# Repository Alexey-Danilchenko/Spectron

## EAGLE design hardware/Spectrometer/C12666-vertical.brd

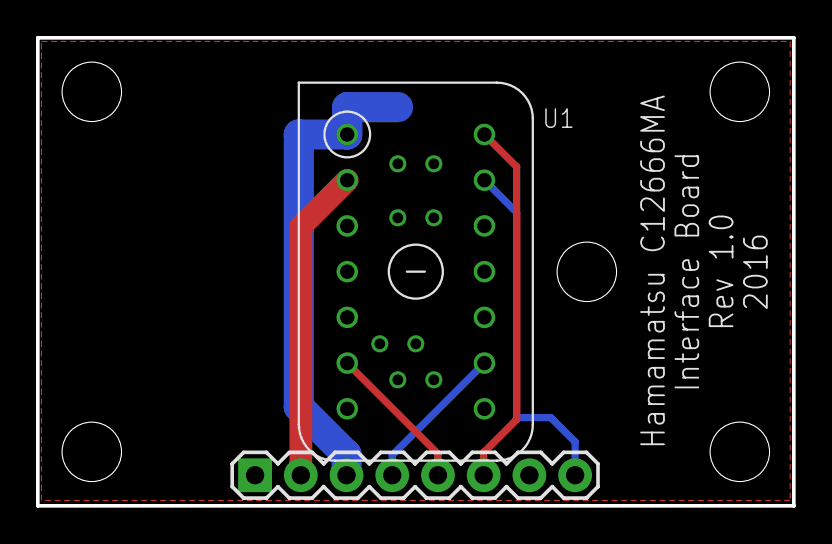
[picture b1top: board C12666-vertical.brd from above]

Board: 2 copper layers, 42.0 x 26.0 mm, 8 parts (1 on the bottom side), 7 nets.

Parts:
C1: 0.1 uF; C0805
JP1: 1X08
STANDOFF1, STANDOFF2, STANDOFF3, STANDOFF4, STANDOFF5: STAND-OFF
U1: MICROSPEC-C12666MA; C12666MA

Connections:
CLK: JP1.5, U1.4
EOS: JP1.6, U1.10
GAIN: JP1.8, U1.9
GND: C1.2, JP1.1, U1.3, U1.5
ST: JP1.4, U1.7
VDD: C1.1, JP1.3, U1.1
VIDEO: JP1.2, U1.2

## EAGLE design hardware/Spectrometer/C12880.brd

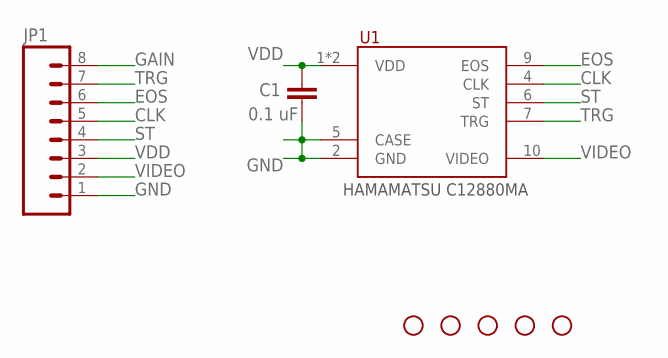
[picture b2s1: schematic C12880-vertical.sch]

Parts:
C1: 0.1 uF; C0805
JP1: M08SILK_FEMALE_PTH; 1X08
STANDOFF1, STANDOFF2, STANDOFF3, STANDOFF4, STANDOFF5: STAND-OFF
U1: MICROSPEC-C12880MA; C12880MA

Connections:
CLK: JP1.5, U1.4 (CLK)
EOS: JP1.6, U1.9 (EOS)
GAIN: JP1.8
GND: C1.2, JP1.1, U1.2 (GND), U1.5 (CASE)
ST: JP1.4, U1.6 (ST)
TRG: JP1.7, U1.7 (TRG)
VDD: C1.1, JP1.3, U1.1 (VDD), U1.3 (VDD)
VIDEO: JP1.2, U1.10 (VIDEO)

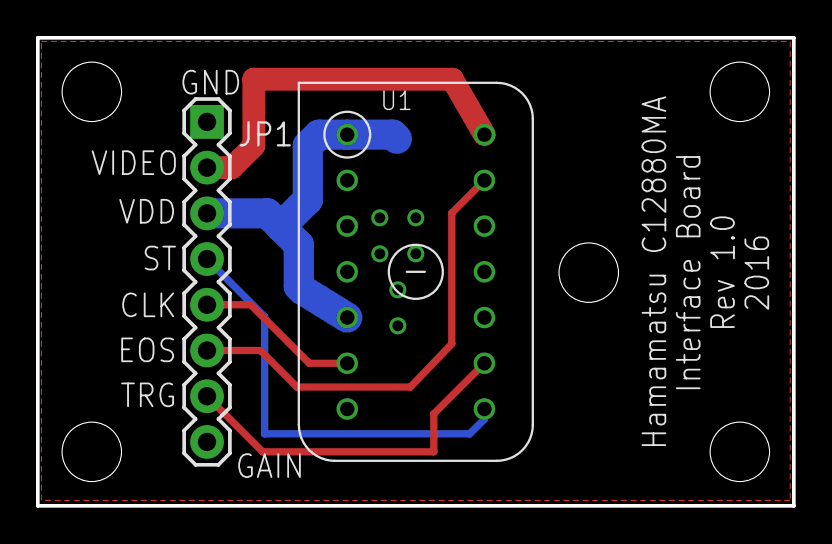
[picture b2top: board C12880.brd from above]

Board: 2 copper layers, 42.0 x 26.0 mm, 8 parts (1 on the bottom side), 7 nets.

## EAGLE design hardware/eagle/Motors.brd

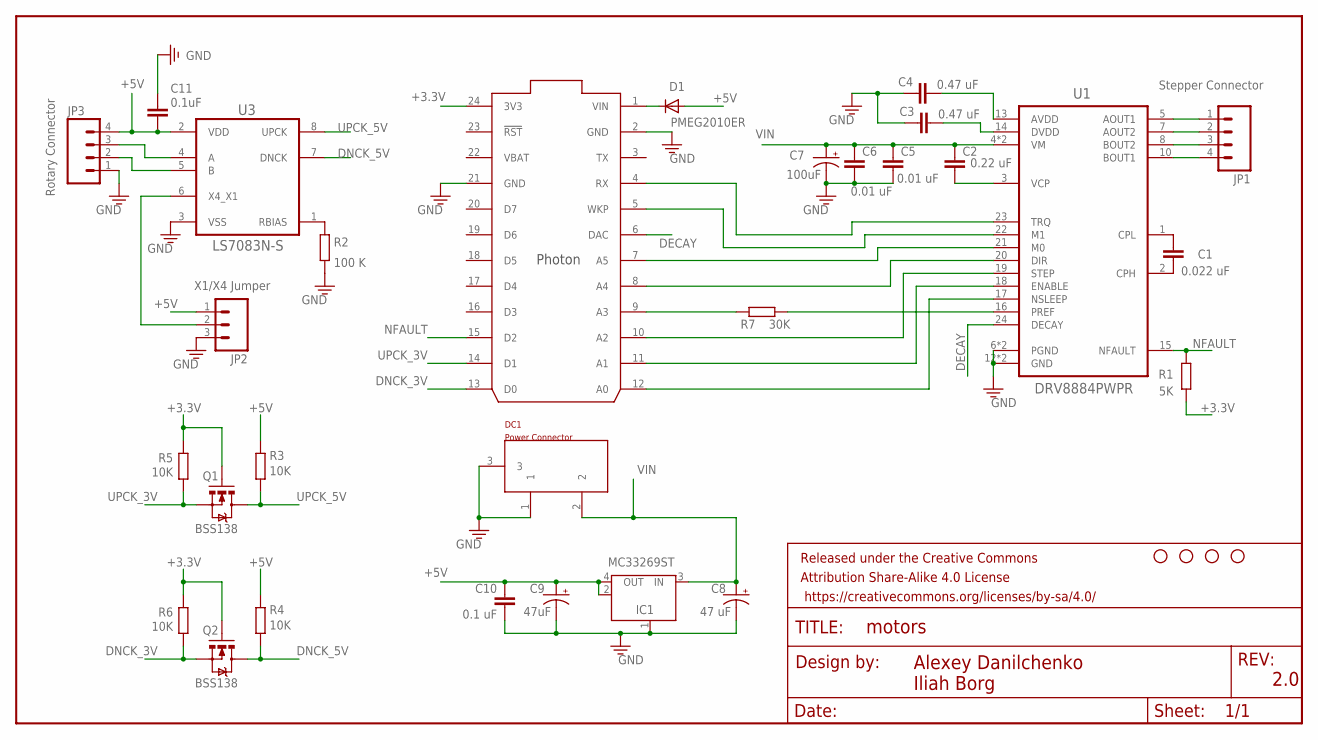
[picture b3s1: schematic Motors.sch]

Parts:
C1: 0.022 uF; C0805
C2: 0.22 uF; C0805
C3, C4: 0.47 uF; C0805
C5, C6: 0.01 uF; C0805
C7: 100uF; CT7343
C8: 47 uF; CT7343
C9: 47uF; CT7343
C10: 0.1 uF; C0805
C11: 0.1uF; C0805
D1: PMEG2010ER; SOD123
DC1: Power Connector; POWERSUPPLY_DC-21MM
FRAME1: FRAME-LETTER; CREATIVE_COMMONS
IC1: MC33269ST; SOT223
JP1: Stepper Connector; 1X04
JP2: X1/X4 Jumper; 1X03
JP3: Rotary Connector; 1X04
Q1, Q2: BSS138; SOT23-3
R1: 5K; R0805
R2: 100 K; R0805
R3, R4, R5, R6: 10K; R0805
R7: 30K; R0805
STANDOFF1, STANDOFF2, STANDOFF3, STANDOFF4: STAND-OFF
U1: DRV8884PWPR; SOP65P640X120-29N
U2: PHOTON_WITH_HEADERS; PHOTON
U3: LS7083N-S; SOIC127P600X175-8N

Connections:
+3.3V: Q1.1 (G), Q2.1 (G), R1.1, R5.1, R6.1, U2.24 (3V3)
+5V: C9.+, C10.1, C11.2, D1.A, IC1.2 (OUT), IC1.4 (OUT), JP2.1, JP3.4, R3.1, R4.1, U3.2 (VDD)
DECAY: U1.24 (DECAY), U2.6 (DAC)
DNCK_3V: Q2.2 (S), R6.2, U2.13 (D0)
DNCK_5V: Q2.3 (D), R4.2, U3.7 (DNCK)
GND: C3.2, C4.2, C5.2, C6.2, C7.-, C8.-, C9.-, C10.2, C11.1, DC1.1, DC1.3, IC1.1 (GND/ADJ), JP2.3, JP3.1, R2.2, U1.6 (PGND), U1.9 (PGND), U1.12 (GND), U1.25 (GND), U2.2 (GND), U2.21 (GND), U3.3 (VSS)
unnamed: U1.18 (ENABLE), U2.11 (A1)
unnamed: C2.2, U1.3 (VCP)
unnamed: C1.1, U1.2 (CPH)
unnamed: C1.2, U1.1 (CPL)
unnamed: U1.22 (M1), U2.5 (WKP)
unnamed: U1.17 (NSLEEP), U2.12 (A0)
unnamed: R7.1, U1.16 (PREF)
unnamed: C4.1, U1.13 (AVDD)
unnamed: C3.1, U1.14 (DVDD)
unnamed: D1.C, U2.1 (VIN)
unnamed: U1.19 (STEP), U2.10 (A2)
unnamed: U1.20 (DIR), U2.8 (A4)
unnamed: U1.21 (M0), U2.7 (A5)
unnamed: U1.23 (TRQ), U2.4 (RX)
unnamed: R7.2, U2.9 (A3)
unnamed: R2.1, U3.1 (RBIAS)
unnamed: JP1.1, U1.5 (AOUT1)
unnamed: JP1.2, U1.7 (AOUT2)
unnamed: JP2.2, U3.6 (X4_X1)
unnamed: JP1.3, U1.8 (BOUT2)
unnamed: JP1.4, U1.10 (BOUT1)
NFAULT: R1.2, U1.15 (NFAULT), U2.15 (D2)
ROTARY_A: JP3.3, U3.4 (A)
ROTARY_B: JP3.2, U3.5 (B)
UPCK_3V: Q1.2 (S), R5.2, U2.14 (D1)
UPCK_5V: Q1.3 (D), R3.2, U3.8 (UPCK)
VBAT: U2.22 (VBAT)
VIN: C2.1, C5.1, C6.1, C7.+, C8.+, DC1.2, IC1.3 (IN), U1.4 (VM), U1.11 (VM)

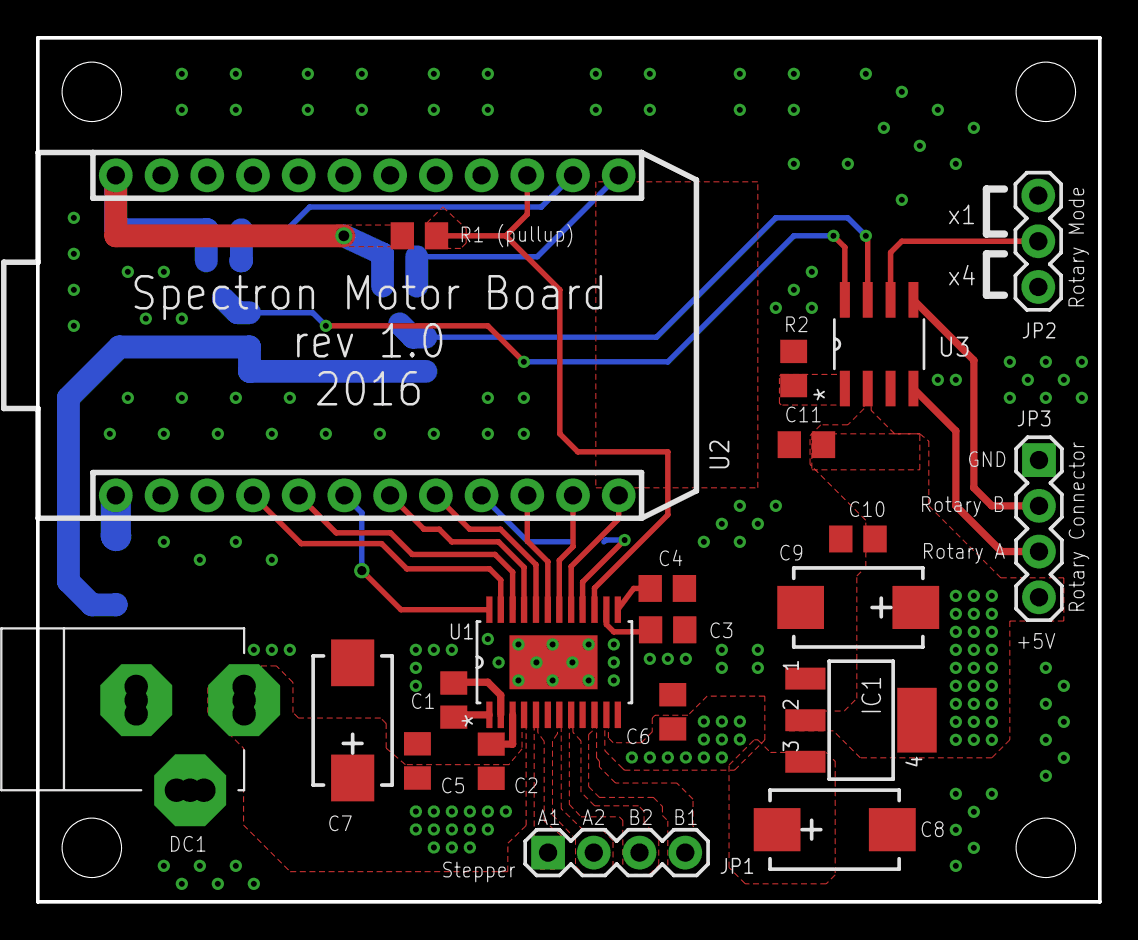
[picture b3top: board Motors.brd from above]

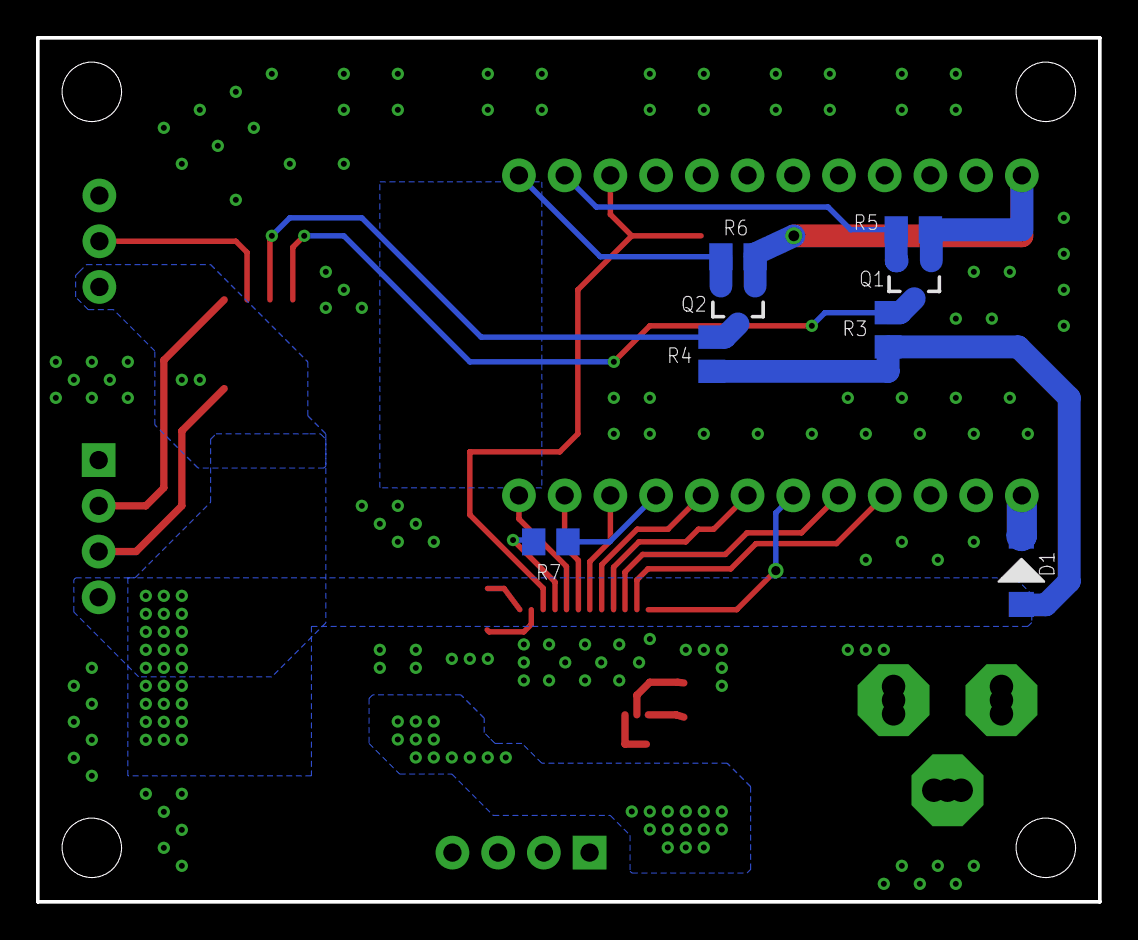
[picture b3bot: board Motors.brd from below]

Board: 2 copper layers, 59.0 x 48.0 mm, 34 parts (8 on the bottom side), 33 nets.

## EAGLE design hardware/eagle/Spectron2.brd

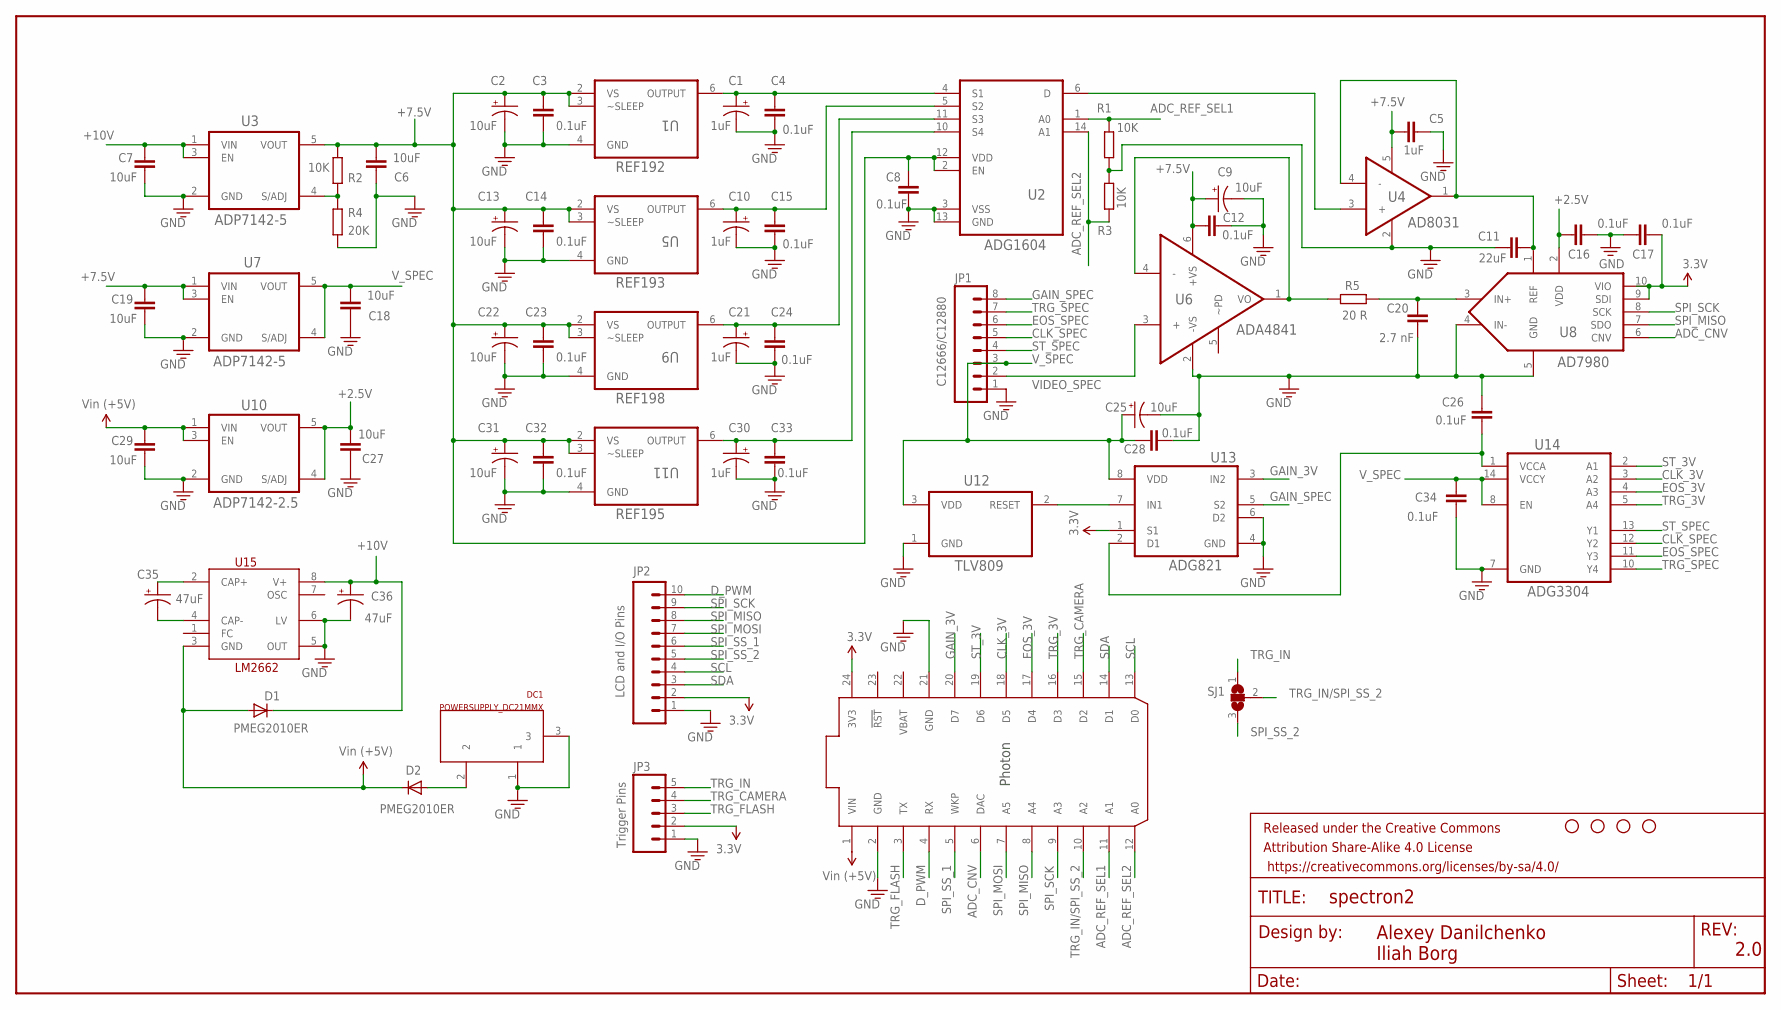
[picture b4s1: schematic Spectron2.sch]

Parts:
C1, C10, C21, C30: 1uF; EIA3216
C2, C9, C13, C22, C25, C31: 10uF; EIA3216
C3, C4, C8, C12, C14, C15, C16, C17, C23, C24, C26, C28, C32, C33, C34: 0.1uF; C0805
C5: 1uF; C0805
C6, C7, C18, C19, C27, C29: 10uF; C0805
C11: 22uF; 1206
C20: 2.7 nF; C0805
C35, C36: 47uF; CT7343
D1, D2: PMEG2010ER; SOD123
DC1: POWERSUPPLY_DC21MMX; POWERSUPPLY_DC-21MM
FRAME1: FRAME-LEDGER; CREATIVE_COMMONS
JP1: C12666/C12880; 1X08
JP2: LCD and I/O Pins; 1X10
JP3: Trigger Pins; 1X05
R1, R2, R3: 10K; R0805
R4: 20K; R0805
R5: 20 R; R0805
SJ1: SJ2W; SJ_2
STANDOFF1, STANDOFF2, STANDOFF3, STANDOFF4: STAND-OFF
U1: REF192; SOIC127P600X175-8N
U2: ADG1604; SOP65P640X120-14N
U3, U7: ADP7142-5; SOT95P280X145-5N
U4: AD8031; SOT95P280X145-5N
U5: REF193; SOIC127P600X175-8N
U6: ADA4841; SOT95P280X145-6N
U8: AD7980; SOP50P490X110-10N
U9: REF198; SOIC127P600X175-8N
U10: ADP7142-2.5; SOT95P280X145-5N
U11: REF195; SOIC127P600X175-8N
U12: TLV809; SOT95P237X112-3N
U13: ADG821; SOP65P490X110-8N
U14: ADG3304; SOP65P640X120-14N
U15: LM2662; SOIC8
U16: PHOTON_WITH_HEADERS; PHOTON

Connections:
3.3V: C17.2, JP2.2, JP3.2, U8.9 (SDI), U8.10 (VIO), U13.1 (S1), U16.24 (3V3)
+2.5V: C16.1, C27.1, U8.2 (VDD), U10.4 (S/ADJ), U10.5 (VOUT)
+7.5V: C2.A (+), C3.2, C5.2, C6.1, C8.2, C9.A (+), C12.2, C13.A (+), C14.2, C19.2, C22.A (+), C23.2, C31.A (+), C32.2, R2.1, U1.2 (VS), U1.3 (~SLEEP), U2.2 (EN), U2.12 (VDD), U3.5 (VOUT), U4.5 (+VS), U5.2 (VS), U5.3 (~SLEEP), U6.6 (+VS), U7.1 (VIN), U7.3 (EN), U9.2 (VS), U9.3 (~SLEEP), U11.2 (VS), U11.3 (~SLEEP)
+10V: C7.2, C36.+, D1.C, U3.1 (VIN), U3.3 (EN), U15.8 (V+)
ADC_CNV: U8.6 (CNV), U16.6 (DAC)
ADC_REF_SEL1: R1.1, U2.1 (A0), U16.11 (A1)
ADC_REF_SEL2: R3.2, U2.14 (A1), U16.12 (A0)
CLK_3V: U14.3 (A2), U16.18 (D5)
CLK_SPEC: JP1.5, U14.12 (Y2)
D_PWM: JP2.10, U16.4 (RX)
EOS_3V: U14.4 (A3), U16.17 (D4)
EOS_SPEC: JP1.6, U14.11 (Y3)
GAIN_3V: U13.3 (IN2), U16.20 (D7)
GAIN_SPEC: JP1.8, U13.5 (S2)
GND: C1.C (-), C2.C (-), C3.1, C4.1, C5.1, C6.2, C7.1, C8.1, C9.C (-), C10.C (-), C11.1, C12.1, C13.C (-), C14.1, C15.1, C16.2, C17.1, C18.2, C19.1, C20.1, C21.C (-), C22.C (-), C23.1, C24.1, C25.C (-), C26.2, C27.2, C28.1, C29.1, C30.C (-), C31.C (-), C32.1, C33.1, C34.1, C36.-, DC1.1, DC1.3, JP1.1, JP2.1, JP3.1, R1.2, R3.1, R4.2, U1.4 (GND), U2.3 (VSS), U2.13 (GND), U3.2 (GND), U4.2 (-VS), U5.4 (GND), U6.2 (-VS), U7.2 (GND), U8.4 (IN-), U8.5 (GND), U9.4 (GND), U10.2 (GND), U11.4 (GND), U12.1 (GND), U13.4 (GND), U13.6 (D2), U14.7 (GND), U15.5 (OUT), U15.6 (LV), U16.2 (GND), U16.21 (GND)
unnamed: R2.2, R4.1, U3.4 (S/ADJ)
unnamed: C11.2, U4.1 (VOUT), U4.4 (-), U8.1 (REF)
unnamed: C21.A (+), C24.2, U2.11 (S3), U9.6 (OUTPUT)
unnamed: R5.2, U6.1 (VO), U6.4 (-)
unnamed: U12.2 (RESET), U13.7 (IN1)
unnamed: C1.A (+), C4.2, U1.6 (OUTPUT), U2.4 (S1)
unnamed: U2.6 (D), U4.3 (+)
unnamed: C10.A (+), C15.2, U2.5 (S2), U5.6 (OUTPUT)
unnamed: C30.A (+), C33.2, U2.10 (S4), U11.6 (OUTPUT)
unnamed: D2.A, DC1.2
unnamed: C20.2, R5.1, U8.3 (IN+)
unnamed: C35.-, U15.4 (CAP-)
unnamed: C35.+, U15.2 (CAP+)
unnamed: C26.1, U13.2 (D1), U14.1 (VCCA)
SCL: JP2.4, U16.13 (D0)
SDA: JP2.3, U16.14 (D1)
SPI_MISO: JP2.8, U8.7 (SDO), U16.8 (A4)
SPI_MOSI: JP2.7, U16.7 (A5)
SPI_SCK: JP2.9, U8.8 (SCK), U16.9 (A3)
SPI_SS_1: JP2.6, U16.5 (WKP)
SPI_SS_2: JP2.5, SJ1.3
ST_3V: U14.2 (A1), U16.19 (D6)
ST_SPEC: JP1.4, U14.13 (Y1)
TRG_3V: U14.5 (A4), U16.16 (D3)
TRG_CAMERA: JP3.4, U16.15 (D2)
TRG_FLASH: JP3.3, U16.3 (TX)
TRG_IN: JP3.5, SJ1.1
TRG_IN/SPI_SS_2: SJ1.2, U16.10 (A2)
TRG_SPEC: JP1.7, U14.10 (Y4)
VBAT: U16.22 (VBAT)
VIDEO_SPEC: JP1.2, U6.3 (+)
VIN: C29.2, D1.A, D2.C, U10.1 (VIN), U10.3 (EN), U15.3 (GND), U16.1 (VIN)
V_SPEC: C18.1, C25.A (+), C28.2, C34.2, JP1.3, U7.4 (S/ADJ), U7.5 (VOUT), U12.3 (VDD), U13.8 (VDD), U14.8 (EN), U14.14 (VCCY)

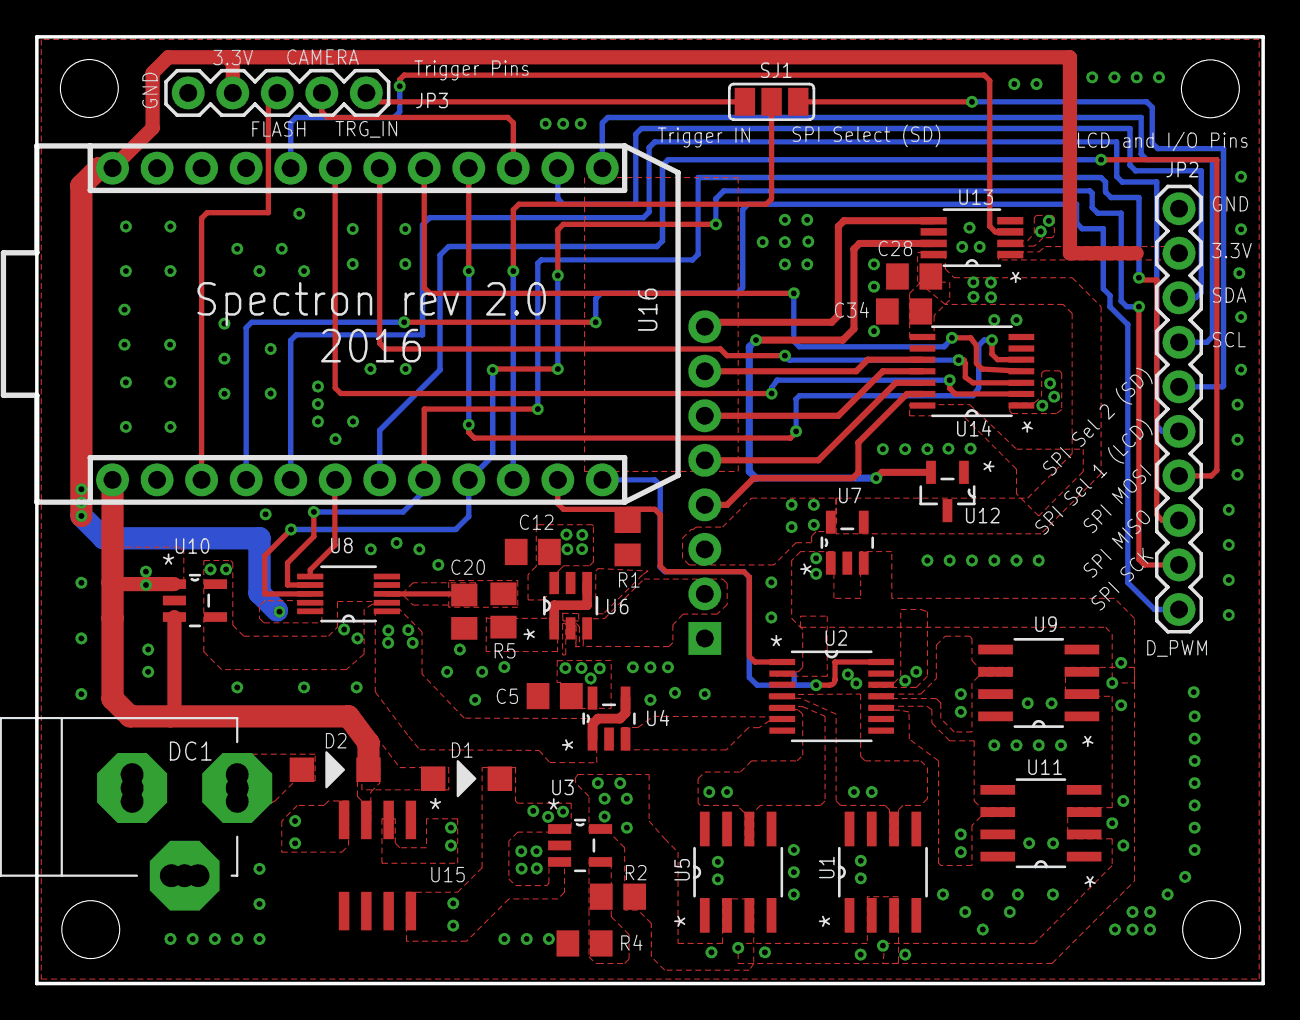
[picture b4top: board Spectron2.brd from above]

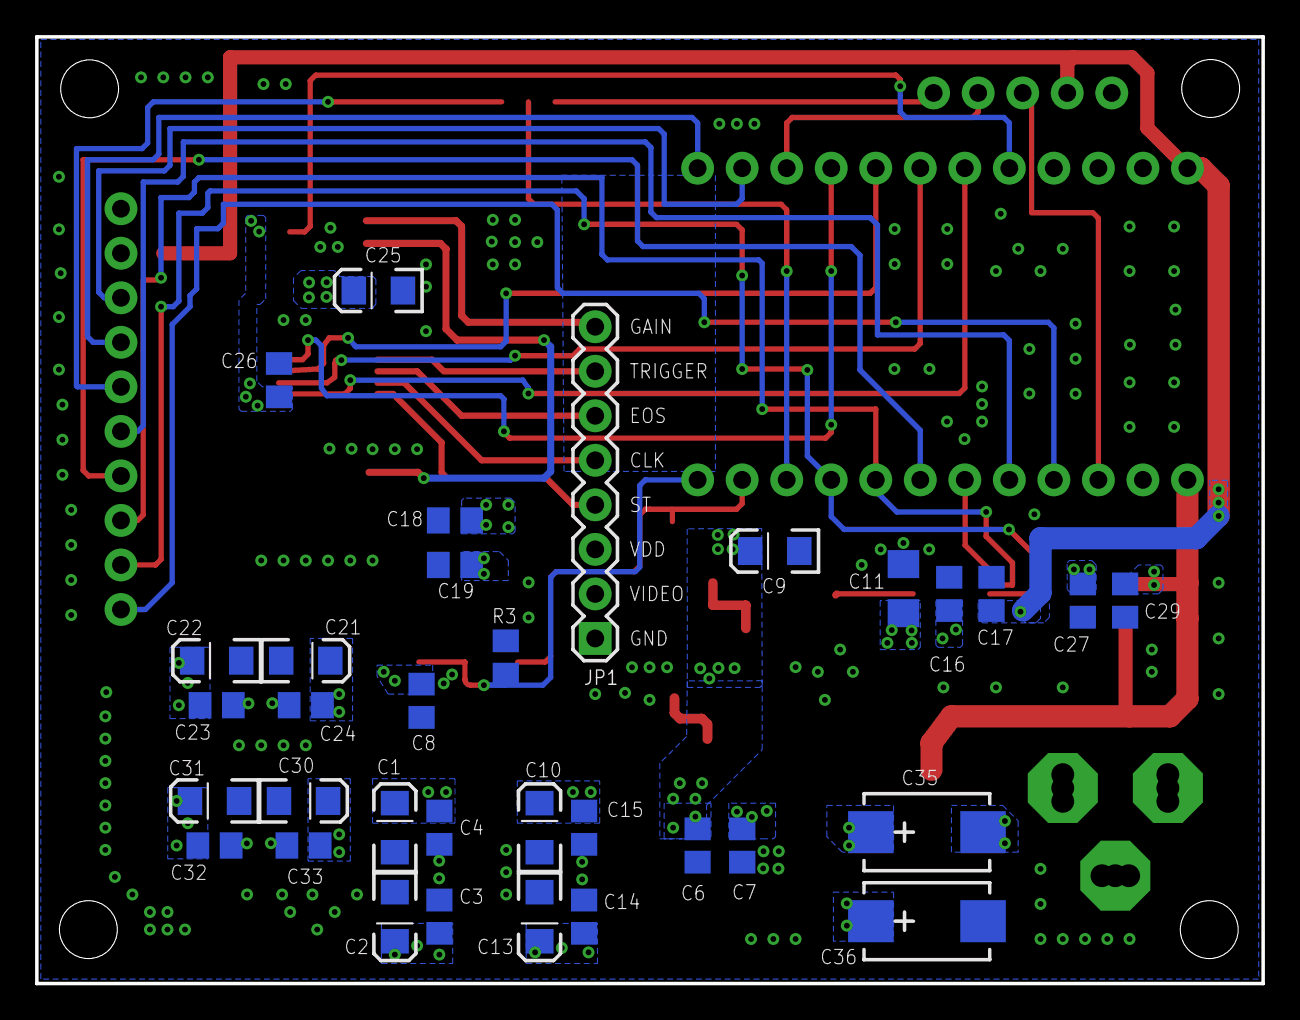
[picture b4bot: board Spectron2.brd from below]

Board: 2 copper layers, 70.0 x 54.0 mm, 69 parts (33 on the bottom side), 47 nets.

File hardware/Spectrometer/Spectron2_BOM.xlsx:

Qty | Value | Device | Package | Parts | Description | MPN | SUPPLIER | Distributor | Distributor Part Number
4 | 1uF | TANT-CAP1206 | EIA3216 | C1, C10, C21, C30 | Tantalum Capacitors - Solid SMD 1uF 25volts 10% A case Molded | 593D105X9025A2TE3 | Vishay | Mouser | 74-593D105X9025A2TE3
1 | 22uF | C-EUC0805 | C0805 | C11 | Multilayer Ceramic Capacitors MLCC - SMD/SMT 0805 22uF 25volts X5R 20% | GRM21BR61E226ME44L | Murata | Mouser | 81-GRM21BR61E226ME4L
6 | 10uF | C-EUC0805 | C0805 | C6, C7,C18, C19, C27, C29 | Multilayer Ceramic Capacitors MLCC - SMD/SMT 0805 10uF 35volts *Derate Voltage/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 | GRM21BC71E106KE11L | Murata | Mouser | 81-GRM21BC8YA106KE1L
1 | 2.7 nF | C-EUC0805 | C0805 | C20 | Multilayer Ceramic Capacitors MLCC - SMD/SMT 0805 2700pF 25volt X7R +/-10% | GRM216R71E272KA01D | Murata | Mouser | 81-GRM216R71E272KA1D
17 | 0.1uF | C-EUC0805 | C0805 | C3, C4, C8, C12, C14, C15, C16, C17, C23, C24, C26, C28, C32, C33, C34 and C1, 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 | Multilayer Ceramic Capacitors MLCC - SMD/SMT 0805 0.1uF 25volts X7R 10% | GRM21BR71E104KA01L | Murata | Mouser | 81-GRM40X104K25L
2 | 47uF | CPOL-USCT7343 | CT7343 | C35, C36 | Tantalum Capacitors - Polymer SMD 35volts 47uF 20% ESR=30mohms | T521X476M035ATE030 | Kemet | Mouser | 80-T521X476M35ATE30
1 | 1uF | C-EUC0805 | C0805 | C5 | Multilayer Ceramic Capacitors MLCC - SMD/SMT | GRM21BR71H105KA12K | Murata | Mouser | 81-GRM21BR71H105KA2K
6 | 10uF | TANT-CAP1206 | EIA3216 | C2, C9, C13, C22, C25, C31 | Tantalum Capacitors - Solid SMD 10UF 25V 10% | F951E106KAAAQ2 | AVX | Mouser | 647-F951E106KAAAQ2
2 | PMEG2010ER | DIODE-SOD123 | SOD123 | D1, D2 | Schottky Diodes & Rectifiers SCHOTTKY LOW VF | PMEG2010ER,115 | NXP | Mouser | 771-PMEG2010ER115
3 | 10K | R-EU_R0805 | R0805 | R1, R2, R3 | Thick Film Resistors - SMD 1/8watt 10Kohms 1% 100ppm | CRCW080510K0FKEA | Vishay | Mouser | 71-CRCW0805-10K-E3
1 | 20K | R-EU_R0805 | R0805 | R4 | Thick Film Resistors - SMD 1/8watt 20Kohms 1% 100ppm | CRCW080520K0FKEA | Vishay | Mouser | 71-CRCW0805-20K-E3
1 | 20 R | R-EU_R0805 | R0805 | R5 | Thick Film Resistors - SMD 0805 20ohm 1% Anti Surge AEC-Q200 | ESR10EZPF20R0 | ROHM Semiconductor | Mouser | 755-ESR10EZPF20R0
1 | AD7980 | AD7980 |  | U8 | Analog to Digital Converters - ADC 16-Bit 1 MSPS | AD7980ARMZ | Analog Devices | Mouser | 584-AD7980ARMZR7
1 | AD8031 | AD8031 |  | U4 | Operational Amplifiers - Op Amps 2.7V 800uA 80Mhz RRIO SGL | AD8031ARTZ-REEL7 | Analog Devices | Mouser | 584-AD8031ARTZ-R7
1 | ADA4841 | ADA4841 |  | U6 | Operational Amplifiers - Op Amps Low Power Low Noise and Distort RRO | ADA4841-1YRJZ-R7 | Analog Devices | Mouser | 584-ADA4841-1YRJZ-R7
1 | ADG1604 | ADG1604 |  | U2 | Multiplexer Switch ICs 4:1 19MHz 950 mOhm CMOS | ADG1604BRUZ | Analog Devices | Mouser | 584-ADG1604BRUZ-R7
1 | ADG3304 | ADG3304 |  | U14 | Translation - Voltage Levels Low VTG 1.15V-5.5V 4-CH Bidirect Logic | ADG3304BRUZ-REEL7 | Analog Devices | Mouser | 584-ADG3304BRUZ-R7
1 | ADG821 | ADG821 |  | U13 | Analogue Switch ICs 500mOhm 5.5V CMOS Dual SPST | ADG821BRMZ-REEL7 | Analog Devices | Mouser | 584-ADG821BRMZ-R7
1 | ADP7142-2.5 | ADP7142 |  | U10 | LDO Voltage Regulators 40V 200mA LDO 2.5Vo | ADP7142AUJZ-2.5-R7 | Analog Devices | Mouser | 584-ADP7142AUJZ2.5R7
2 | ADP7142-5.0 | ADP7142 |  | U3, U7 | LDO Voltage Regulators 40V 200mA LDO 5.0Vo | ADP7142AUJZ-5.0-R7 | Analog Devices | Mouser | 584-ADP7142AUJZ5.0R7
1 | LM2662 | LM2662 |  | U15 | Voltage Regulators - Switching Regulators Switched Capacitor Vtg Cnvtr | LM2662MX/NOPB | Texas Instruments | Mouser | 926-LM2662MX/NOPB
1 | REF192 | REF192 |  | U1 | Voltage References 2.5V Prec Micropwr LDO Low VRef | REF192GSZ | Analog Devices | Mouser | 584-REF192GSZ-R7
1 | REF193 | REF193 |  | U5 | Voltage References 3V Prec Micropwr LDO | REF193GSZ | Analog Devices | Mouser | 584-REF193GSZ
1 | REF195 | REF195 |  | U11 | Voltage References 5V Prec Micropwr LDO Low VRef | REF195GSZ | Analog Devices | Mouser | 584-REF195GSZ-R
1 | REF198 | REF198 |  | U9 | Voltage References 4.096V Prec Micropwr LDO Low VRef | REF198GSZ | Analog Devices | Mouser | 584-REF198GSZ-R
1 | TLV809 | TLV809 |  | U12 | Supervisory Circuits 3Pin Supply Vltg Sup | TLV809K33DBVR | Texas Instruments | Mouser | 595-TLV809K33DBVR
1 | C12666/C12880 | Preci-Dip 350-80-108-00-006101 |  | JP1 | Header 8 | 714-87-112-31-012101 | Preci-Dip | RS-Online | 702-0060
1 | Trigger Pins | M05PTH | 1X05 | JP3 | Header 5
1 | POWERSUPPLY DC21MMX | POWERSUPPLY DC21MMX | POWERSUPPLY_DC-21MM | DC1 | DC Power Connectors Power Jacks | PJ-102AH | CUI Inc. | Mouser | 490-PJ-102AH
1 | PHOTON without headers | PHOTON without headers | PHOTON | U16 |  |  |  | Mouser
4 | Photon socket, sensor board socket | Preci-Dip 714-87-112-31-012101 |  |  |  | 714-87-112-31-012101 | Preci-Dip | DIGIKEY | 1212-1166-ND
2 | Photon headers for the sockets above | Preci-Dip 350-80-112-00-006101 |  |  |  | 350-80-112-00-006101, 350-PP-1NN-00-006101 series | Preci-Dip | RS-Online | 702-0095
1 | Spectrometer stand | MICRO SPECTROMETER |  |  | Hamamatsu Micro-Spectrometer C12666MA or C12880MA, part ordered is Preci-Dip st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 | 115-87-314-41-003101 | Preci-Dip | DIGIKEY | 1212-1045-ND

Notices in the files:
parts and their libraries:
SparkFun-Connectors: Licensing: Creative Commons ShareAlike 4.0 International - https://creativecommons.org/licenses/by-sa/4.0
SparkFun-Aesthetics: Released under the Creative Commons
SparkFun-Aesthetics: https://creativecommons.org/licenses/by-sa/4.0
